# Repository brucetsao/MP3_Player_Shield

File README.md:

MP3 Player Shield 
NOTE: This branch is currently under Revision
==================

[  
*MP3 Player Shield (SEN-11084)*](https://www.sparkfun.com/products/10628)

The MP3 Player Shield has a microSD socket, VS1053 decoder IC and all the supporting circuitry to be able to decode and play MP3s from an Arduino.

Repository Contents
-------------------
* **/firmware** - Multiple examples of how to read MP3 files and send them to the VS1053.
* **/hardware** - All Eagle design files (.brd, .sch)

License Information
-------------------

The hardware is released under [Creative Commons Share-alike 3.0](http://creativecommons.org/licenses/by-sa/3.0/).  

All other code is open source so please feel free to do anything you want with it; you buy me a beer if you use this and we meet someday ([Beerware license](http://en.wikipedia.org/wiki/Beerware)).

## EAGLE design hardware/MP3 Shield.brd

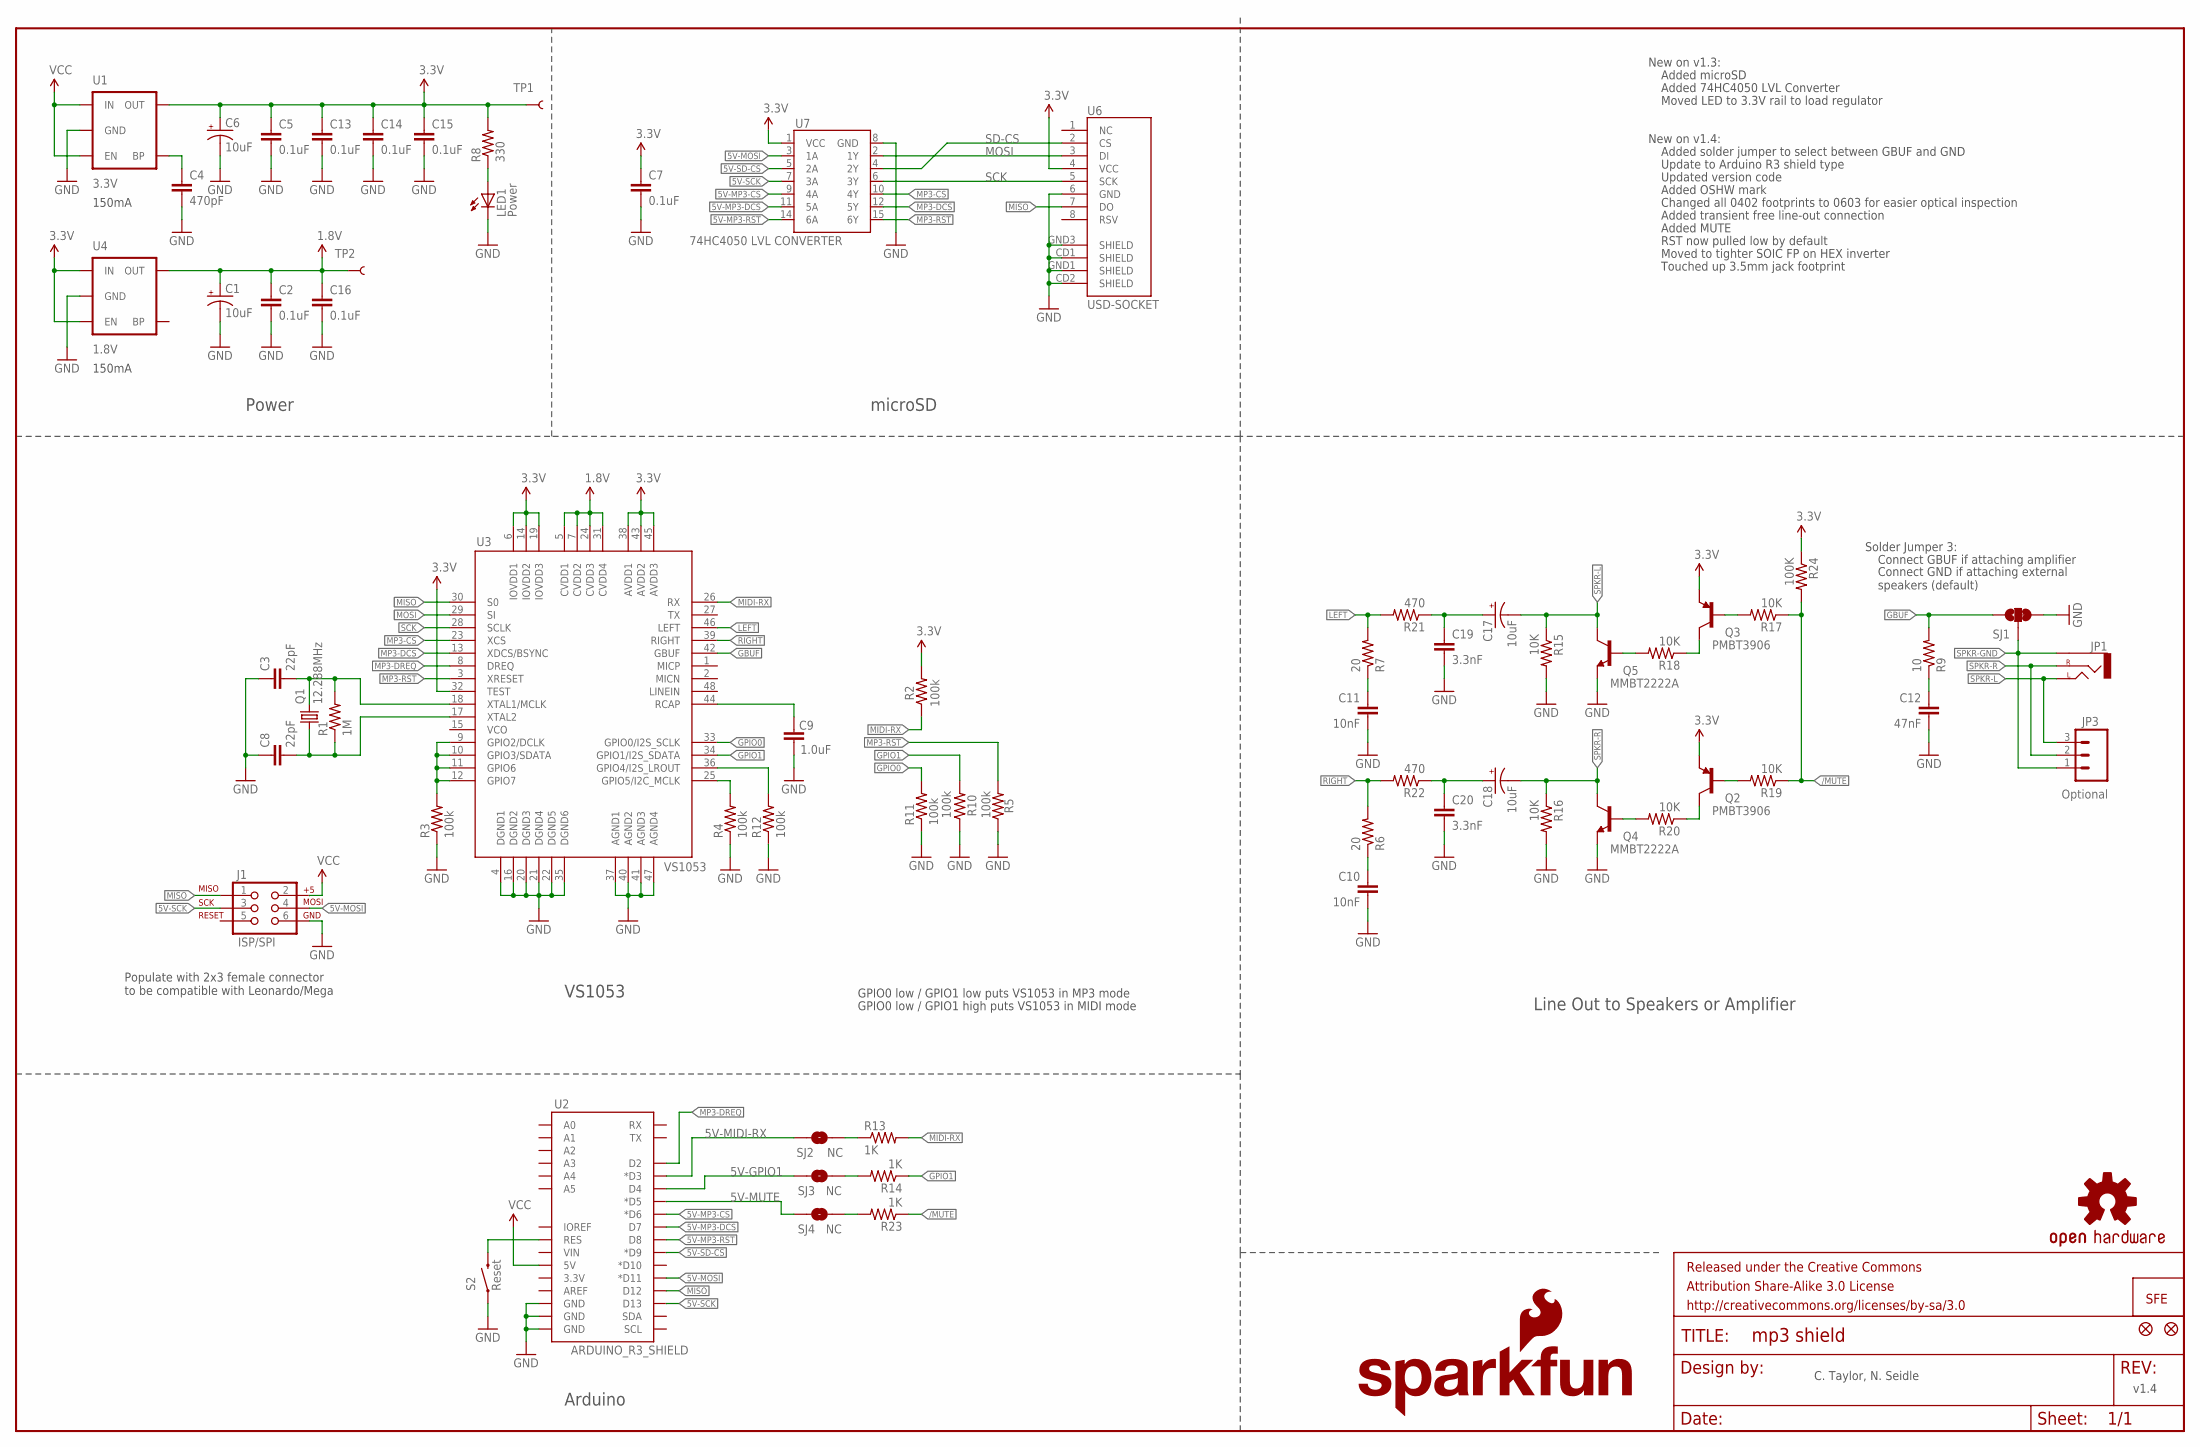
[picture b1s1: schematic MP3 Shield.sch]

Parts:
C1, C6, C17, C18: 10uF; EIA3216
C2, C5, C7, C13, C14, C15, C16: 0.1uF; 0603-CAP
C3, C8: 22pF; 0603-CAP
C4: 470pF; 0603-CAP
C9: 1.0uF; 0603-CAP
C10, C11: 10nF; 0603-CAP
C12: 47nF; 0603-CAP
C19, C20: 3.3nF; 0603-CAP
FRAME1: FRAME-LEDGER; CREATIVE_COMMONS
J1: ISP/SPI; 2X3
JP1: AUDIO-JACKSMD2; AUDIO-JACK-3.5MM-SMD
JP3: Optional; 1X03
LED1: Power; LED-0603
LOGO1: OSHW-LOGOS; OSHW-LOGO-S
LOGO2: SFE_LOGO_NAME_FLAME.1_INCH; SFE_LOGO_NAME_FLAME_.1
Q1: 12.288MHz; CRYSTAL-SMD-5X3
Q2, Q3: PMBT3906; SOT23-3
Q4, Q5: MMBT2222A; SOT23-3
R1: 1M; 0603-RES
R2, R3, R4, R5, R10, R11, R12: 100k; 0603-RES
R6, R7: 20; 0603-RES
R8: 330; 0603-RES
R9: 10; 0603-RES
R13, R14, R23: 1K; 0603-RES
R15, R16, R17, R18, R19, R20: 10K; 0603-RES
R21, R22: 470; 0603-RES
R24: 100K; 0603-RES
S2: Reset; TACTILE_SWITCH_SMD
SJ1: SOLDERJUMPER_2WAYPASTE2&3; SJ_3_PASTE2&3
SJ2, SJ3, SJ4: NC; SJ_2S-TRACE
TP1, TP2: TEST-POINT3X5; PAD.03X.05
U1: 3.3V; SOT23-5
U2: ARDUINO_R3_SHIELD; UNO_R3_SHIELD
U3: VS1053; LQFP-48
U4: 1.8V; SC70
U6: USD-SOCKET; MICRO-SD-SOCKET-PP
U7: 74HC4050 LVL CONVERTER; SO016
U$4, U$5: FIDUCIAL1X2; FIDUCIAL-1X2
U$8: LOGO-SFENEW; SFE-NEW-WEBLOGO

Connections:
1.8V: C1.A (+), C2.1, C16.1, TP2.P$1, U3.5 (CVDD1), U3.7 (CVDD2), U3.24 (CVDD3), U3.31 (CVDD4), U4.5 (OUT)
3.3V: C5.1, C6.A (+), C7.1, C13.1, C14.1, C15.1, Q2.2 (E), Q3.2 (E), R2.2, R8.2, R24.1, TP1.P$1, U1.5 (OUT), U3.6 (IOVDD1), U3.14 (IOVDD2), U3.19 (IOVDD3), U3.32 (TEST), U3.38 (AVDD1), U3.43 (AVDD2), U3.45 (AVDD3), U4.1 (IN), U4.3 (EN), U6.4 (VCC), U7.1 (VCC)
5V-GPIO1: SJ3.2, U2.D4
5V-MIDI-RX: SJ2.1, U2.D3 (*D3)
5V-MOSI: J1.4, U2.D11 (*D11), U7.3 (1A)
5V-MP3-CS: U2.D6 (*D6), U7.9 (4A)
5V-MP3-DCS: U2.D7, U7.11 (5A)
5V-MP3-RST: U2.D8, U7.14 (6A)
5V-MUTE: SJ4.2, U2.D5 (*D5)
5V-SCK: J1.3, U2.D13, U7.7 (3A)
5V-SD-CS: U2.D9 (*D9), U7.5 (2A)
/MUTE: R17.1, R19.1, R23.1, R24.2
ARST: S2.3 (2), U2.RES
G1: R3.2, U3.9 (GPIO2/DCLK), U3.10 (GPIO3/SDATA), U3.11 (GPIO6), U3.12 (GPIO7)
G2: R4.2, U3.25 (GPIO5/I2C_MCLK)
GBUF: R9.2, SJ1.1, U3.42 (GBUF)
GND: C1.C (-), C2.2, C3.1, C4.2, C5.2, C6.C (-), C7.2, C8.1, C9.1, C10.2, C11.2, C12.2, C13.2, C14.2, C15.2, C16.2, C19.2, C20.2, J1.6, LED1.C, Q4.2 (E), Q5.2 (E), R3.1, R4.1, R5.1, R10.1, R11.1, R12.1, R15.2, R16.2, S2.1, SJ1.3, U1.2 (GND), U2.GND@0 (GND), U2.GND@1 (GND), U2.GND@2 (GND), U3.4 (DGND1), U3.16 (DGND2), U3.20 (DGND3), U3.21 (DGND4), U3.22 (DGND5), U3.35 (DGND6), U3.37 (AGND1), U3.40 (AGND2), U3.41 (AGND3), U3.47 (AGND4), U4.2 (GND), U6.6 (GND), U6.CD1 (SHIELD), U6.CD2 (SHIELD), U6.GND1 (SHIELD), U6.GND3 (SHIELD), U7.8 (GND)
GPIO0: R11.2, U3.33 (GPIO0/I2S_SCLK)
GPIO1: R10.2, R14.1, U3.34 (GPIO1/I2S_SDATA)
GPIO4: R12.2, U3.36 (GPIO4/I2S_LROUT)
LEFT: R7.2, R21.2, U3.46 (LEFT)
MIDI-RX: R2.1, R13.2, U3.26 (RX)
MISO: J1.1, U2.D12, U3.30 (S0), U6.7 (DO)
MOSI: U3.29 (SI), U6.3 (DI), U7.2 (1Y)
MP3-CS: U3.23 (XCS), U7.10 (4Y)
MP3-DCS: U3.13 (XDCS/BSYNC), U7.12 (5Y)
MP3-DREQ: U2.D2, U3.8 (DREQ)
MP3-RST: R5.2, U3.3 (XRESET), U7.15 (6Y)
unnamed: Q4.1 (B), R20.2
unnamed: C12.1, R9.1
unnamed: C10.1, R6.1
unnamed: R14.2, SJ3.1
unnamed: C11.1, R7.1
unnamed: LED1.A, R8.1
unnamed: Q2.3 (C), R20.1
unnamed: R13.1, SJ2.2
unnamed: C3.2, Q1.3 (2), R1.2, U3.18 (XTAL1/MCLK)
unnamed: C8.2, Q1.1, R1.1, U3.17 (XTAL2)
unnamed: Q2.1 (B), R19.2
unnamed: Q5.1 (B), R18.2
unnamed: R23.2, SJ4.1
unnamed: Q3.3 (C), R18.1
unnamed: Q3.1 (B), R17.2
unnamed: C18.A (+), C20.1, R22.1
unnamed: C17.A (+), C19.1, R21.1
unnamed: C4.1, U1.4 (BP)
RCAP: C9.2, U3.44 (RCAP)
RIGHT: R6.2, R22.2, U3.39 (RIGHT)
SCK: U3.28 (SCLK), U6.5 (SCK), U7.6 (3Y)
SD-CS: U6.2 (CS), U7.4 (2Y)
SPKR-GND: JP1.SLEEVE, JP3.1, SJ1.2
SPKR-L: C17.C (-), JP1.TIP (LEFT), JP3.3, Q5.3 (C), R15.1
SPKR-R: C18.C (-), JP1.RING (RIGHT), JP3.2, Q4.3 (C), R16.1
VCC: J1.2, U1.1 (IN), U1.3 (EN), U2.5V

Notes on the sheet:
GPIO0 low / GPIO1 high puts VS1053 in MIDI mode
C. Taylor, N. Seidle
New on v1.3:
GPIO0 low / GPIO1 low puts VS1053 in MP3 mode
microSD
Power
Line Out to Speakers or Amplifier
Arduino
VS1053
Moved LED to 3.3V rail to load regulator
Added microSD
Added 74HC4050 LVL Converter
New on v1.4:
Added solder jumper to select between GBUF and GND
Connect GBUF if attaching amplifier
Connect GND if attaching external speakers (default)
Update to Arduino R3 shield type
Updated version code
Added OSHW mark
Changed all 0402 footprints to 0603 for easier optical inspection
Added transient free line-out connection
Added MUTE
Solder Jumper 3:
150mA
v1.4
RST now pulled low by default
Populate with 2x3 female connector to be compatible with Leonardo/Mega
Moved to tighter SOIC FP on HEX inverter
Touched up 3.5mm jack footprint

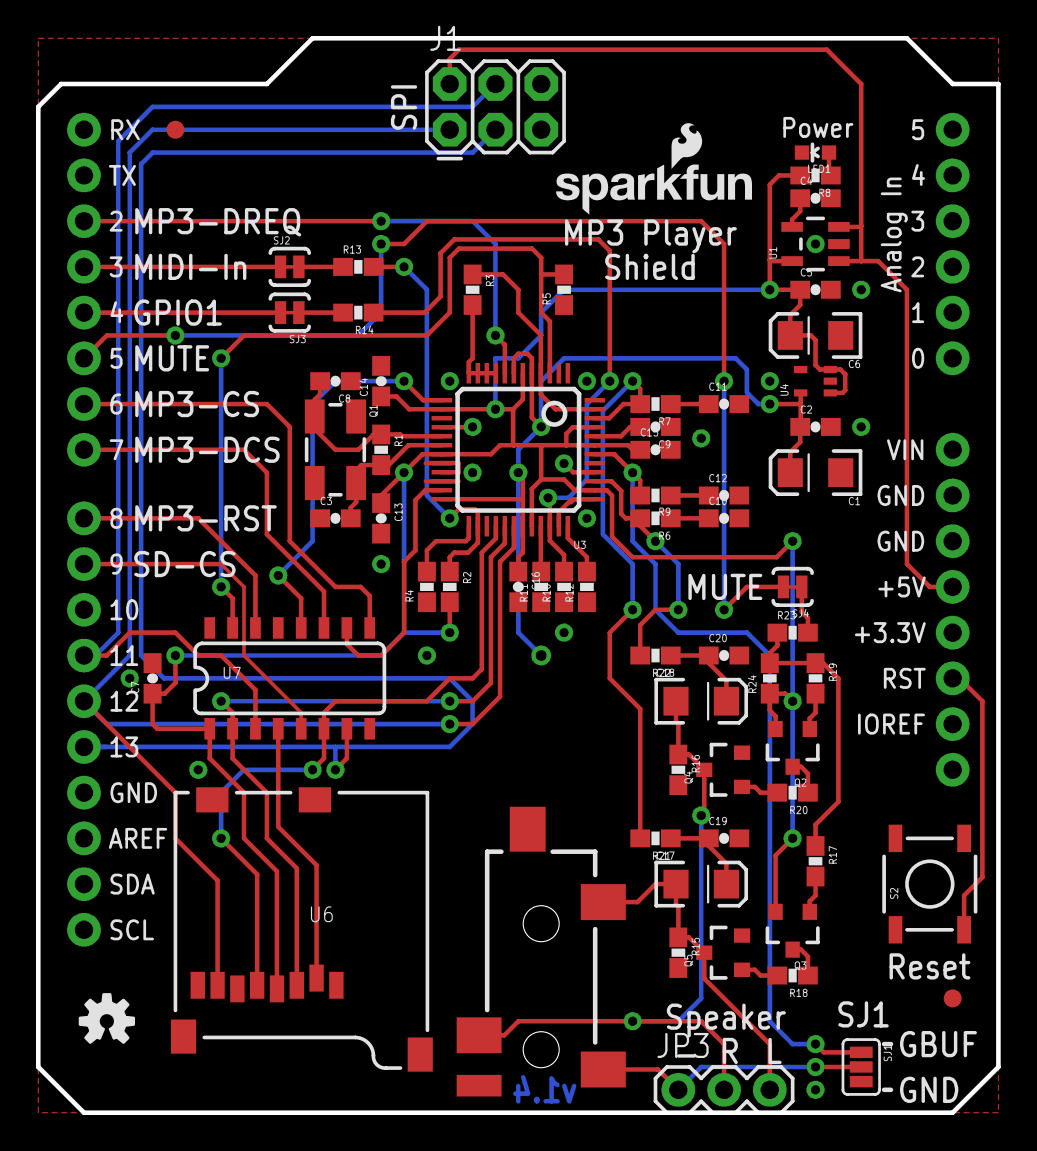
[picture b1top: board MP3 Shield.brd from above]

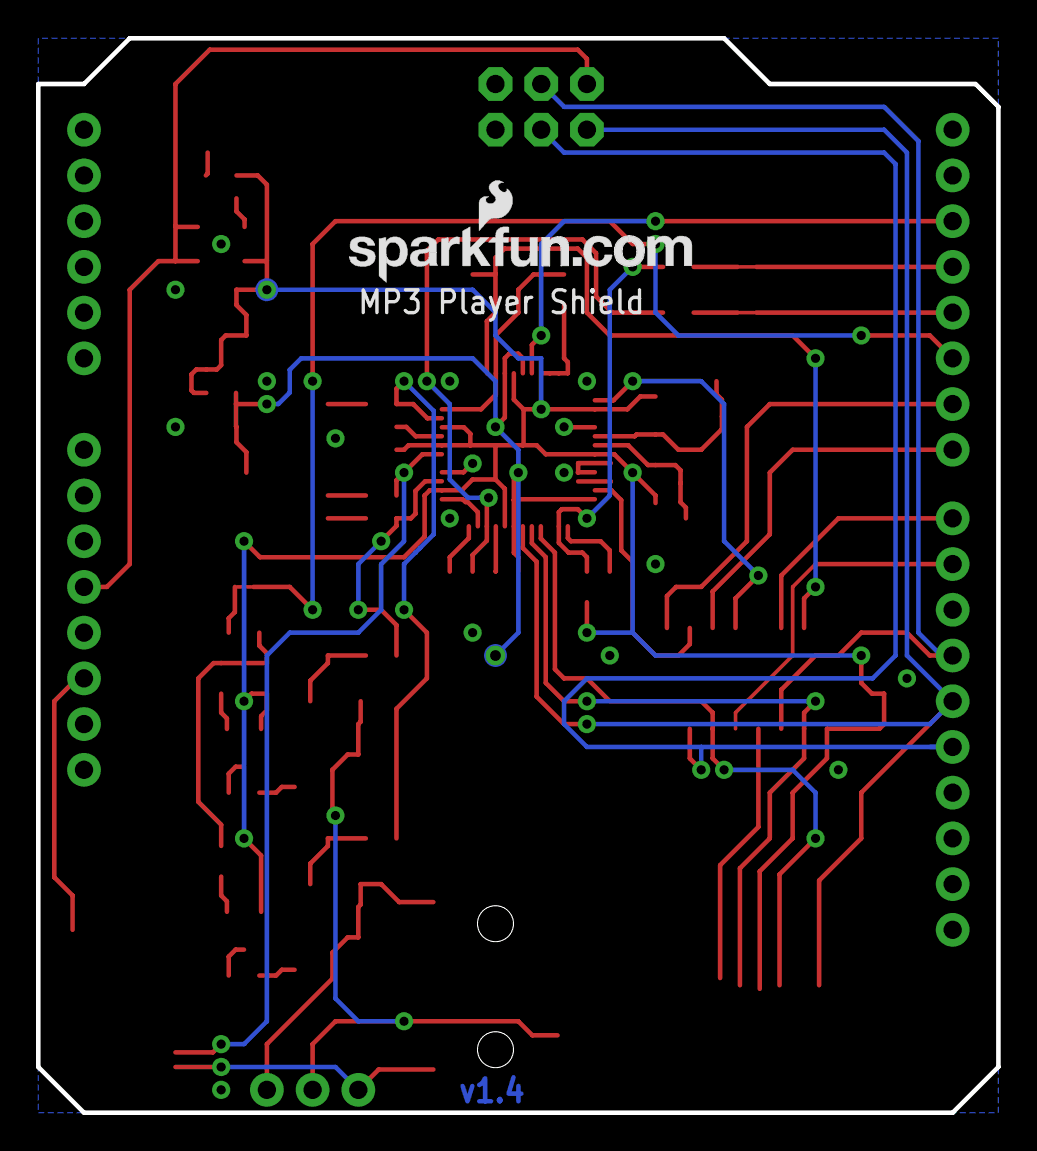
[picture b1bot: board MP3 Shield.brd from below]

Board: 2 copper layers, 53.3 x 59.7 mm, 72 parts (3 on the bottom side), 54 nets.

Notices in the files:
parts and their libraries:
SparkFun-Passives: Licensing: CC v3.0 Share-Alike You are welcome to use this library for commercial purposes.
SparkFun-Aesthetics: Released under the Creative Commons Attribution Share-Alike 3.0 License
SparkFun-Aesthetics: Released under the Creative Commons
